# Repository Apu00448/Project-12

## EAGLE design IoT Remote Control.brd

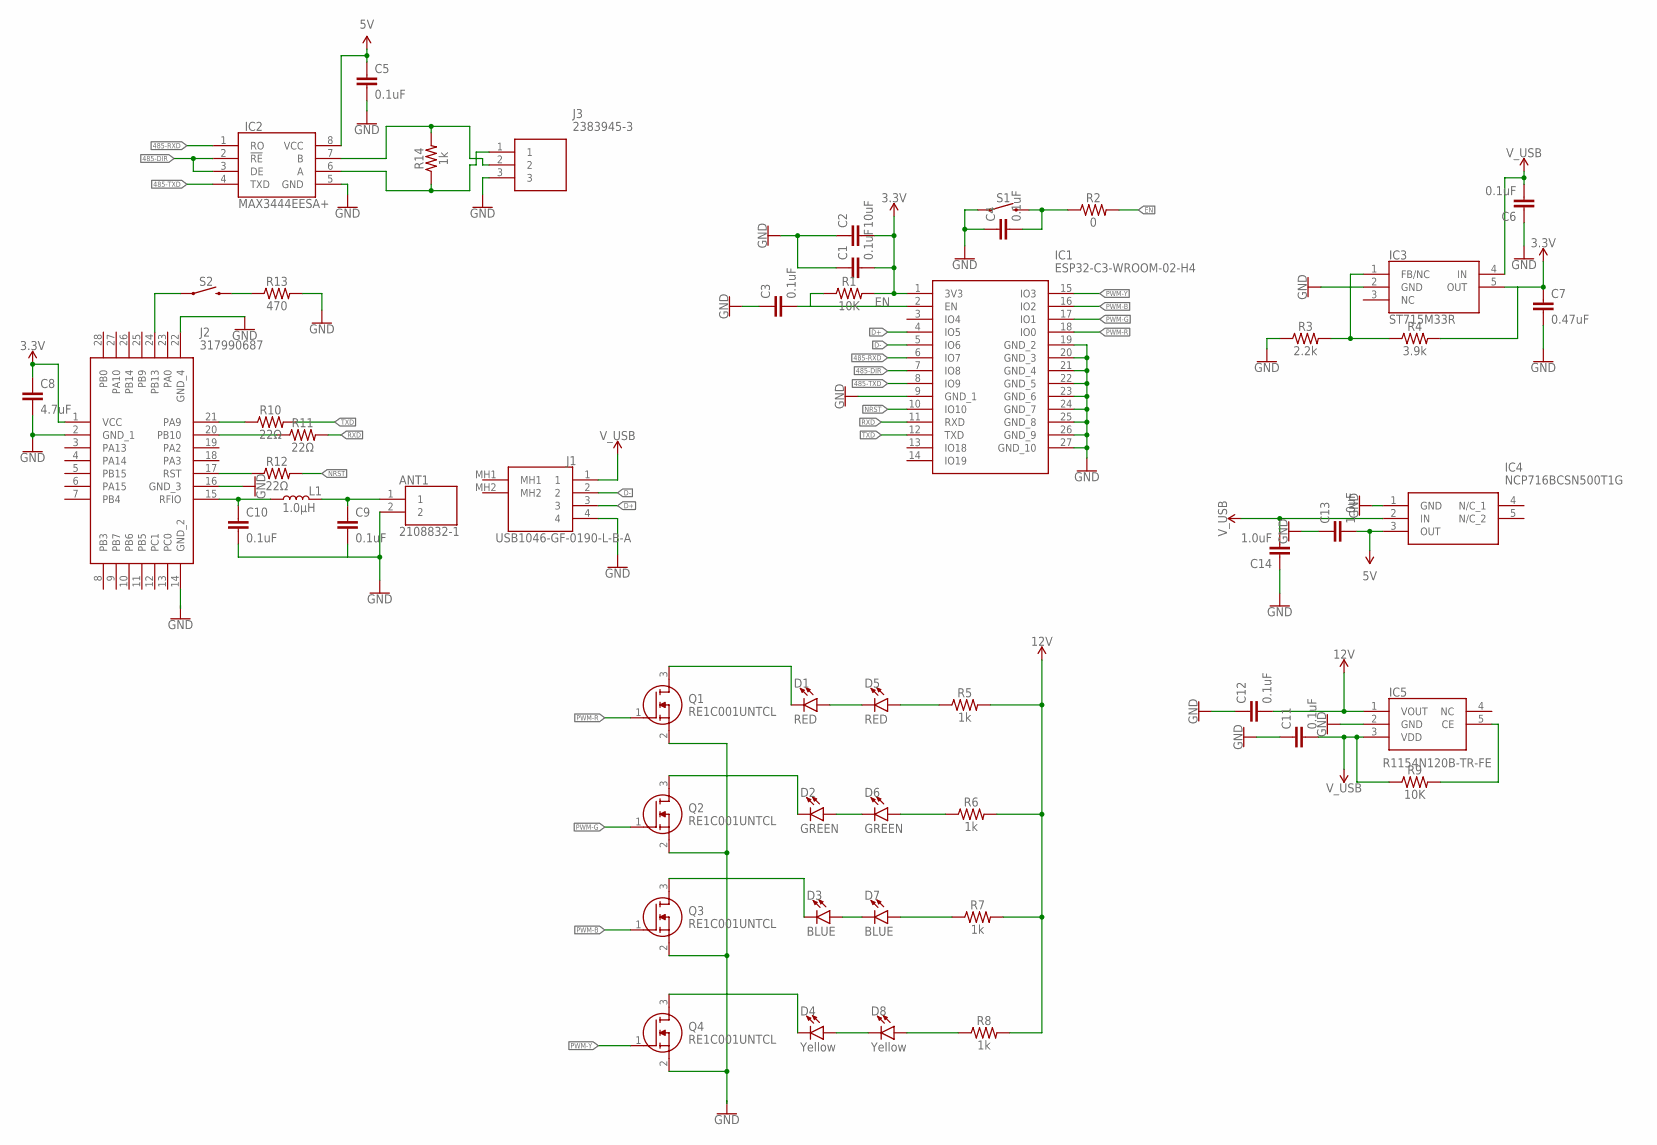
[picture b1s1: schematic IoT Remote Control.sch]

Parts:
ANT1: 2108832-1; 21088321
C1, C3, C4, C5, C6, C9, C10, C11, C12: 0.1uF; 0402-TIGHT
C2: 10uF; 0402-TIGHT
C7: 0.47uF; 0402-TIGHT
C8: 4.7uF; 0402-TIGHT
C13, C14: 1.0uF; 0402-TIGHT
D1, D5: RED; LED-0603
D2, D6: GREEN; LED-0603
D3, D7: BLUE; LED-0603
D4, D8: Yellow; LED-0603
IC1: ESP32-C3-WROOM-02-H4; ESP32C3WROOM02H4
IC2: MAX3444EESA+; SOIC127P600X175-8N
IC3: ST715M33R; SOT95P280X145-5N
IC4: NCP716BCSN500T1G; SOT95P275X110-5N
IC5: R1154N120B-TR-FE; SOT95P280X130-5N
J1: USB1046-GF-0190-L-B-A; USB1046GF0190LBA
J2: 317990687
J3: 2383945-3; 23839453
L1: 1.0μH; 0805-WIDE
Q1, Q2, Q3, Q4: RE1C001UNTCL; SOTFL50P160X85-3N
R1, R9: 10K; 0402-TIGHT
R2: 0; 0402-TIGHT
R3: 2.2k; 0402-TIGHT
R4: 3.9k; 0603
R5, R6, R7, R8, R14: 1k; 0402-TIGHT
R10, R11, R12: 22Ω; 0402-TIGHT
R13: 470; 0402-TIGHT
S1, S2: MOMENTARY-SWITCH-SPST-SMD-4.6X2.8MM; TACTILE_SWITCH_SMD_4.6X2.8MM

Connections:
3.3V: C1.2, C2.2, C7.1, C8.1, IC1.1 (3V3), IC3.5 (OUT), J2.1 (VCC), R1.2, R4.2
5V: C5.1, C13.2, IC2.8 (VCC), IC4.3 (OUT)
12V: C12.2, IC5.1 (VOUT), R5.2, R6.2, R7.2, R8.2
485-DIR: IC1.7 (IO8), IC2.2 (!RE), IC2.3 (DE)
485-RXD: IC1.6 (IO7), IC2.1 (RO)
485-TXD: IC1.8 (IO9), IC2.4 (TXD)
D+: IC1.4 (IO5), J1.3
D-: IC1.5 (IO6), J1.2
EN: C3.2, IC1.2 (EN), R2.2
GND: ANT1.2, C1.1, C2.1, C3.1, C4.1, C5.2, C6.1, C7.2, C8.2, C10.2, C11.1, C12.1, C13.1, C14.1, IC1.9 (GND_1), IC1.19 (GND_2), IC1.20 (GND_3), IC1.21 (GND_4), IC1.22 (GND_5), IC1.23 (GND_6), IC1.24 (GND_7), IC1.25 (GND_8), IC1.26 (GND_9), IC1.27 (GND_10), IC2.5 (GND), IC3.2 (GND), IC4.1 (GND), IC5.2 (GND), J1.4, J2.2 (GND_1), J2.14 (GND_2), J2.16 (GND_3), J2.22 (GND_4), J3.3, Q1.2 (S), Q2.2 (S), Q3.2 (S), Q4.2 (S), R3.1, R13.2, S1.1, S1.2 (1)
unnamed: C4.2, R2.1, S1.3 (2), S1.4 (2)
unnamed: IC3.1 (FB/NC), R3.2, R4.1
unnamed: D3.A, D7.C
unnamed: D1.C, Q1.3 (D)
unnamed: D2.C, Q2.3 (D)
unnamed: D7.A, R7.1
unnamed: D8.A, R8.1
unnamed: D3.C, Q3.3 (D)
unnamed: D4.C, Q4.3 (D)
unnamed: D4.A, D8.C
unnamed: D6.A, R6.1
unnamed: IC5.5 (CE), R9.2
unnamed: D2.A, D6.C
unnamed: D1.A, D5.C
unnamed: D5.A, R5.1
unnamed: J2.21 (PA9), R10.1
unnamed: J2.20 (PB10), R11.1
unnamed: C10.1, J2.15 (RFIO), L1.1
unnamed: ANT1.1, C9.1, L1.2
unnamed: J2.17 (RST), R12.1
unnamed: J2.24 (PB13), S2.1, S2.2 (1)
unnamed: R13.1, S2.3 (2), S2.4 (2)
unnamed: IC2.7 (B), J3.2, R14.2
unnamed: IC2.6 (A), J3.1, R14.1
NRST: IC1.10 (IO10), R12.2
PWM-B: IC1.16 (IO2), Q3.1 (G)
PWM-G: IC1.17 (IO1), Q2.1 (G)
PWM-R: IC1.18 (IO0), Q1.1 (G)
PWM-Y: IC1.15 (IO3), Q4.1 (G)
RXD: IC1.11 (RXD), R11.2
TXD: IC1.12 (TXD), R10.2
V_USB: C6.2, C11.2, C14.2, IC3.4 (IN), IC4.2 (IN), IC5.3 (VDD), J1.1, R9.1

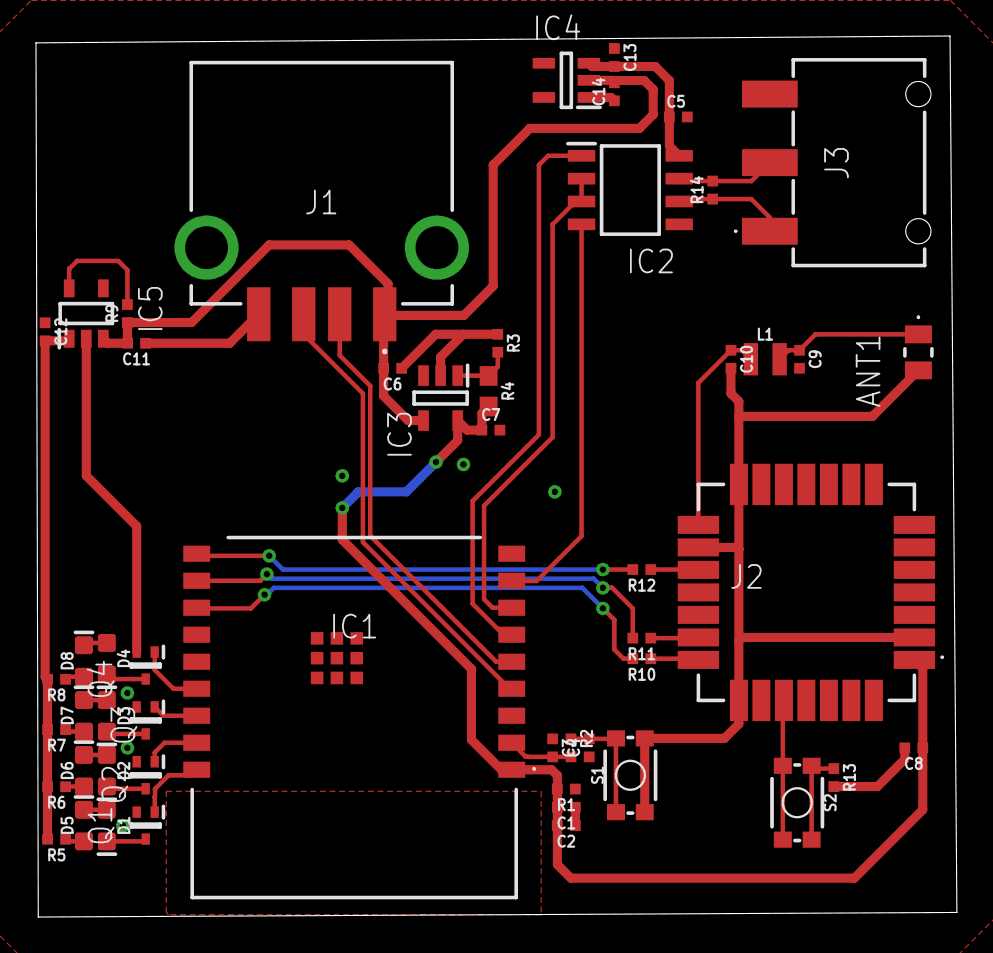
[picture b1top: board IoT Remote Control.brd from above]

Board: 2 copper layers, 51.2 x 48.9 mm, 52 parts (0 on the bottom side), 42 nets.

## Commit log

2024-01-03 IoT Remote COntrol-- Eagle

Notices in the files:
parts and their libraries:
SparkFun-Capacitors: Licensing: Creative Commons ShareAlike 4.0 International - https://creativecommons.org/licenses/by-sa/4.0
